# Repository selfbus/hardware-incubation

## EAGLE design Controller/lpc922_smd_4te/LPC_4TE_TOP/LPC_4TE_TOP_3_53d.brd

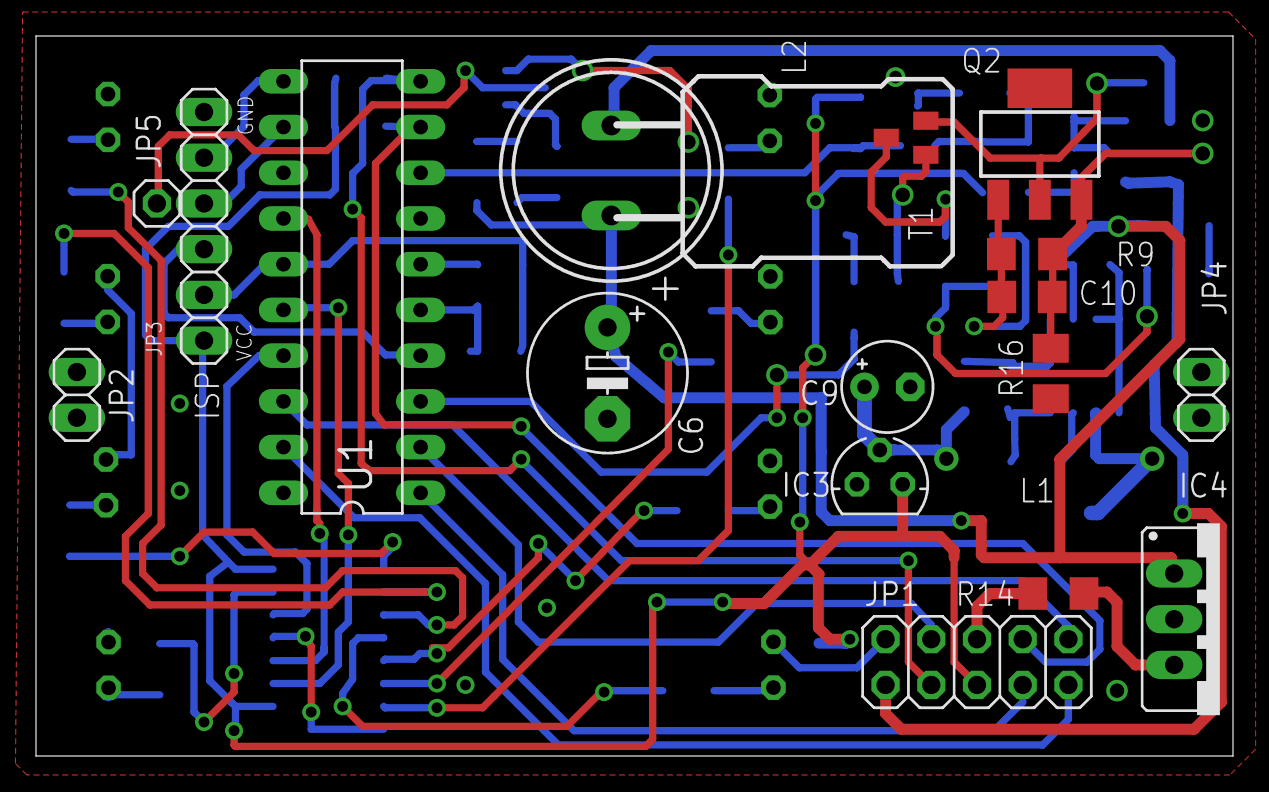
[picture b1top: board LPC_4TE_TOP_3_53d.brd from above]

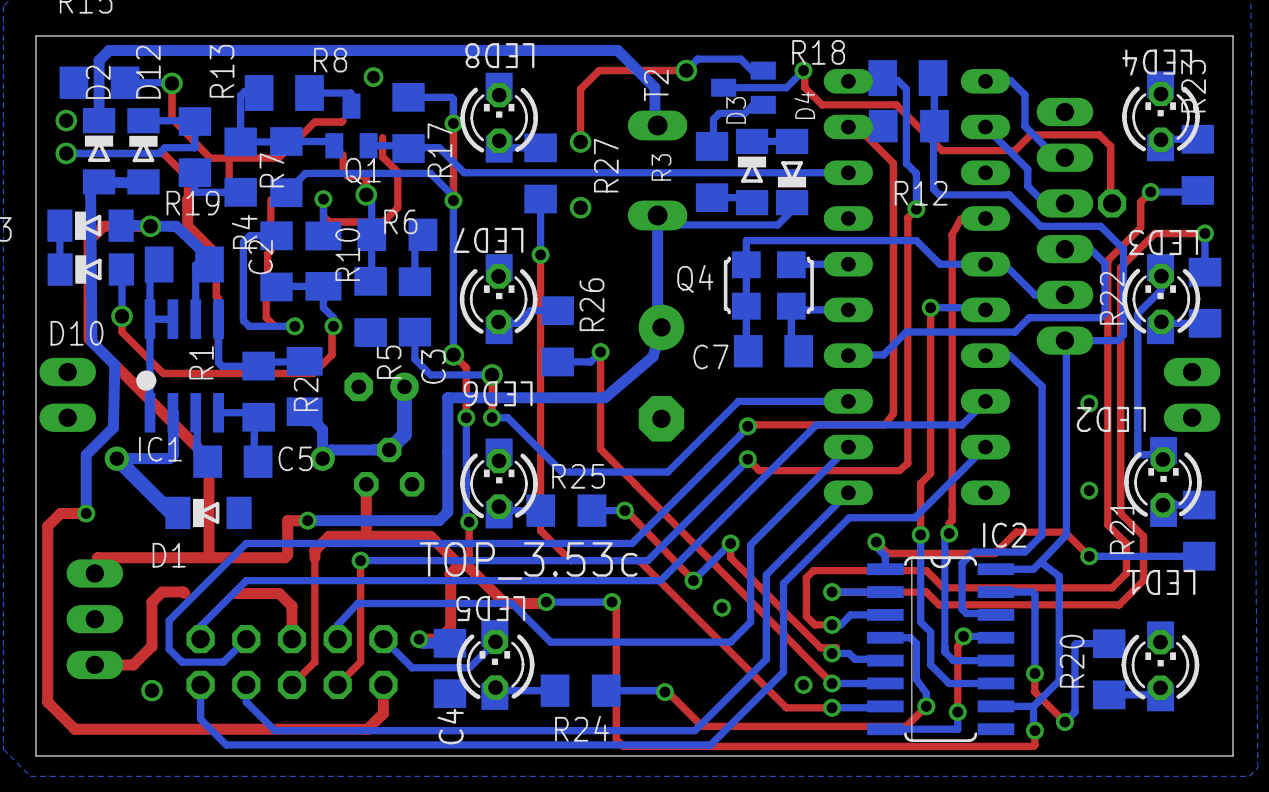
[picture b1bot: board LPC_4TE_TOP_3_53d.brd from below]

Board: 2 copper layers, 66.5 x 40.0 mm, 74 parts (56 on the bottom side), 58 nets.

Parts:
C2, C7: 100n; C1206
C3, C10: 10n; C1206
C4: 1µ16V; C1206
C5: 470p; C1206
C6: 100µ35V; E5-8,5
C9: 100µ16V; E2,5-5
D1: BAT46; MINIMELF
D2, D12: 1N4148; MINIMELF
D3: 12V; MINIMELF
D4, D10: 7,5V; MINIMELF
D13: 4148; MINIMELF
IC1: MC34063AD; SOIC8
IC2: 74HC595D; SO16
IC3: MCP1702-33; 79LXX
IC4: 7812; 78XXS
JP1: 2X05
JP2, JP4: 1X02
JP3: 1X06
JP5: 1X01
L1: 220µH; 2200-11.43
L2: 150mH; SD12_1000
LED1, LED2, LED3, LED4, LED5, LED6, LED7, LED8: LED3MM
LED9, LED10, LED11, LED12, LED13, LED14, LED15, LED16: CHIPLED_1206
Q1: BC856; SOT23-BEC
Q2: BCP52; SOT223
Q4: ASF
R1: 1k2; R1206
R2: 3k6; M1206
R3: 470k; R1206
R4, R9: 1k; R1206
R5: 100k; R1206
R6: 5k6; R1206
R7: 82k; R1206
R8: 47k; M1206
R10: 2k2; M1206
R12: 3k3; R1206
R13, R17: 10k; R1206
R14: ?; R1206
R15: 5R6; R1206
R16: 100k; M1206
R18: 3k3; M1206
R19: 3R3; M1206
R20, R21, R22, R23, R24, R25, R26, R27: R1206
T1, T2: BC848; SOT23
U1: 89LPC922; DIL20

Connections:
DRAIN: R10.1, T1.3
EIB+: D2.A, D12.A, JP1.1
EIBIN: Q1.E, R17.2, U1.8
EIB_DC: C6.+, D4.C, D13.A, IC1.6, IC4.IN, L2.2, R19.2
EIB_SEND: C3.2, U1.3
GATE: R5.2, R6.2, T1.1
GND: C4.1, C5.2, C6.-, C7.2, C9.-, D1.A, IC1.4, IC2.8, IC2.13, IC3.GND, IC4.GND, JP1.2, JP3.6, JP4.1, JP4.2, LED1.K, LED2.K, LED3.K, LED4.K, LED5.K, LED6.K, LED7.K, LED8.K, LED9.C, LED10.C, LED11.C, LED12.C, LED13.C, LED14.C, LED15.C, LED16.C, Q1.C, Q4.2, R1.1, R5.1, R8.1, R15.2, R16.1, T2.2, U1.5
INT0: JP1.8, R12.2, U1.9
unnamed: LED1.A, LED9.A, R20.2
unnamed: LED2.A, LED10.A, R21.2
unnamed: LED3.A, LED11.A, R22.2
unnamed: C10.1, Q2.1, R4.2, R9.1
unnamed: C3.1, R6.1
unnamed: C10.2, D12.C, Q2.3, R9.2, R13.2, R16.2
unnamed: Q2.2, R15.1, T1.2
unnamed: D2.C, L2.1
unnamed: JP3.5, U1.11
unnamed: LED4.A, LED12.A, R23.2
unnamed: LED5.A, LED13.A, R24.2
unnamed: IC4.OUT, R14.2
unnamed: LED6.A, LED14.A, R25.2
unnamed: LED7.A, LED15.A, R26.2
unnamed: JP3.3, U1.4
unnamed: D3.C, D4.A
unnamed: LED8.A, LED16.A, R27.2
unnamed: D3.A, R3.1
unnamed: R3.2, T2.1
unnamed: JP5.1, T2.3
unnamed: IC2.15, R20.1
unnamed: IC2.1, R21.1
unnamed: JP3.4, U1.12
unnamed: Q4.3, U1.6
unnamed: C9.+, IC3.IN, L1.1, R2.2
unnamed: IC2.2, R22.1
unnamed: IC2.3, R23.1
unnamed: IC2.7, R27.1
unnamed: C2.2, Q1.B, R7.1, R8.2
unnamed: IC2.6, R26.1
unnamed: IC2.5, R25.1
unnamed: IC2.4, R24.1
unnamed: IC1.5, R1.2, R2.1
unnamed: D1.C, IC1.2, L1.2
unnamed: C5.1, IC1.3
unnamed: D10.A, R4.1, R10.2
unnamed: D10.C, D13.C
unnamed: IC1.1, IC1.7, IC1.8, R19.1
unnamed: C2.1, R13.1
P0.0: JP1.7, U1.1
P0.2: JP1.9, U1.19
P0.3: JP1.10, U1.18
P04: IC2.14, U1.17
P05: IC2.11, U1.16
P06: IC2.12, U1.14
PROG: JP1.4, U1.2
PWM: JP1.3, R18.2, U1.10
VCC: C4.2, IC2.10, IC2.16, IC3.OUT, JP1.5, JP3.1, R7.2, R12.1, R17.1, R18.1
VCC_LPC: C7.1, JP3.2, Q4.1, Q4.4, U1.15
VDD: JP1.6, R14.1

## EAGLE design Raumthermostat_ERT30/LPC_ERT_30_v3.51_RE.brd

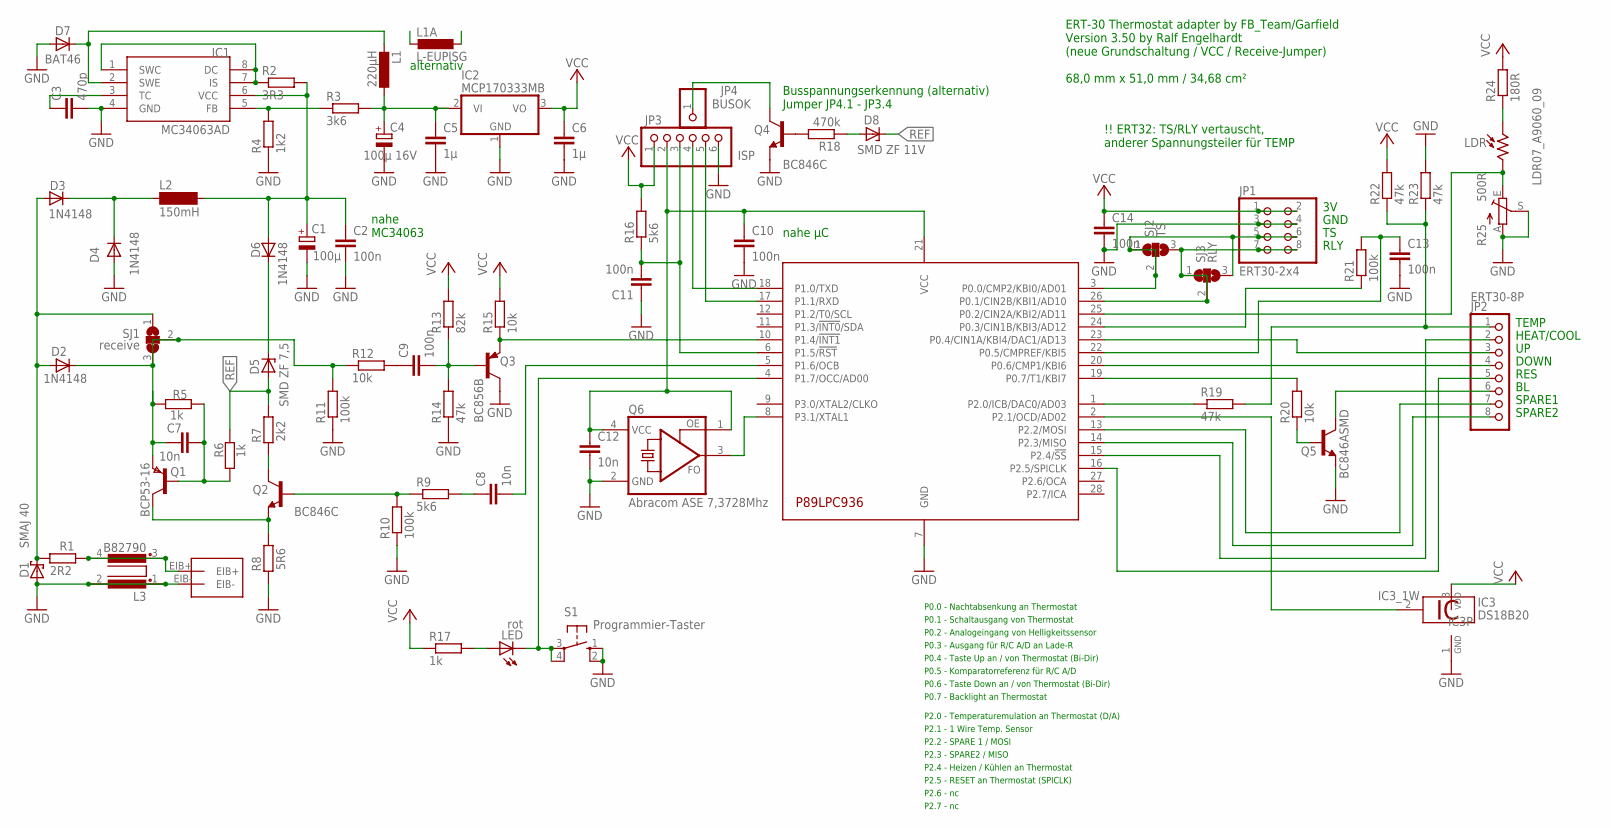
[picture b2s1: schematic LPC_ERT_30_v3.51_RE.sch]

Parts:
C1: 100µ; 153CLV-0605
C2, C9, C10, C11, C13, C14: 100n; C1206
C3: 470p; C1206
C4: 100µ 16V; 153CLV-0605
C5, C6: 1µ; C1206
C7, C8, C12: 10n; C1206
D1: SMAJ 40; SMB
D2, D3, D4, D6: 1N4148; MINIMELF
D5: SMD ZF 7,5; MINIMELF
D7: BAT46; MINIMELF
D8: SMD ZF 11V; MINIMELF
IC1: MC34063AD; SOIC8
IC2: MCP170333MB; SOT89
IC3: DS18B20; TO92-
JP1: ERT30-2x4; 2X04
JP2: ERT30-8P; PS-G-8
JP3: ISP; 1X06_SELFBUS
JP4: BUSOK; 1X01_SELFBUS
L1: 220µH; PIS24XX
L1A: L-EUPISG; PISG
L2: 150mH; SD12_1000
L3: B82790
LDR: LDR07_A9060_09; A90XX
LED: rot; CHIPLED_1206
LPC: P98LPC936 TSOP28; TSSOP28
Q1: BCP53-16; SOT223
Q2, Q4: BC846C; SOT23
Q3: BC856B; SOT23-BEC
Q5: BC846ASMD; SOT23
Q6: Abracom ASE 7,3728Mhz; ASFL3
R1: 2R2; R1206
R2: 3R3; R1206
R3: 3k6; R1206
R4: 1k2; R1206
R5, R6, R17: 1k; R1206
R7: 2k2; R1206
R8: 5R6; R1206
R9, R16: 5k6; R1206
R10, R11, R21: 100k; R1206
R12, R15, R20: 10k; R1206
R13: 82k; R1206
R14, R19, R22, R23: 47k; R1206
R18: 470k; R1206
R24: 180R; R1206
R25: 500R; CA6H
S1: Programmier-Taster; B3F-10XX
SJ1: receive; SJ_2
SJ2: TS; SJ_2
SJ3: RLY; SJ_2
U$5: EIB-CON

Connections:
+5V: C4.+, C5.1, IC2.2 (VI), IC2.2@1 (VI1), L1.2 (1), L1A.2, R3.2
/RST: C11.2, JP3.3, LPC.6 (P1.5/!RST), R16.1
AD0.3_TEMP: LPC.1 (P2.0/ICB/DAC0/AD03), R19.1
AD11_LDR: LDR.P$2 (2), LPC.25 (P0.2/CIN2A/KBI2/AD11), R25.E
AD12: LPC.24 (P0.3/CIN1B/KBI3/AD12), R21.1
BUS_OK: JP4.1, Q4.3 (C)
CLK: LPC.8 (P3.1/XTAL1), Q6.3 (FO)
CMP_REF: C13.1, LPC.22 (P0.5/CMPREF/KBI5), R21.2
EIB+: D1.C, D2.A, D3.A, R1.2, SJ1.1
GND: C1.-, C2.2, C3.2, C4.-, C5.2, C6.2, C10.2, C11.1, C12.2, C13.2, C14.2, D1.A, D4.A, D7.A, IC1.4 (GND), IC2.1 (GND), IC3.1 (GND), JP1.3, JP1.4, JP3.6, L3.1, L3.2, LPC.7 (GND), Q3.C, Q4.2 (E), Q5.2 (E), Q6.2 (GND), R4.1, R8.1, R10.1, R11.1, R14.1, R23.2, R25.A, R25.S, S1.1 (S), S1.2 (S1), U$5.EIB-
unnamed: C7.2, D2.C, Q1.3 (E), R5.2, R11.2, R12.1, SJ1.2, SJ1.3
unnamed: C9.2, Q3.B, R13.1, R14.2
unnamed: Q4.1 (B), R18.2
unnamed: Q2.3 (C), R7.1
unnamed: D3.C, D4.C, L2.1
unnamed: D8.A, R18.1
unnamed: C7.1, Q1.1 (B), R5.1, R6.2
unnamed: Q1.2 (C), Q1.4 (C), Q2.2 (E), R8.2
unnamed: C9.1, R12.2
unnamed: Q5.1 (B), R20.1
unnamed: JP2.6, Q5.3 (C)
unnamed: Q2.1 (B), R9.1, R10.2
unnamed: LDR.P$1 (1), R24.1
unnamed: C8.1, R9.2
unnamed: L3.3, L3.4, R1.1, U$5.EIB+
unnamed: D5.C, D6.C
unnamed: LED.A, R17.2
unnamed: JP2.1, R19.2, R22.1, R23.1
P0.0_TS: JP1.5, JP1.6, LPC.3 (P0.0/CMP2/KBI0/AD01), SJ2.1, SJ2.2, SJ3.3
P0.1_RLY: JP1.7, JP1.8, LPC.26 (P0.1/CIN2B/KBI1/AD10), SJ2.3, SJ3.1, SJ3.2
P0.4_UP: JP2.3, LPC.23 (P0.4/CIN1A/KBI4/DAC1/AD13)
P0.6_DOWN: JP2.4, LPC.20 (P0.6/CMP1/KBI6)
P0.7_BL: LPC.19 (P0.7/T1/KBI7), R20.2
P1.4_REC: LPC.10 (P1.4/!INT1), Q3.E, R15.1
P1.6_SENT: C8.2, LPC.5 (P1.6/OCB)
P1.7_PROG: LED.C, LPC.4 (P1.7/OCC/AD00), S1.3, S1.4 (P1)
P2.1_DS1820_1W1W: IC3.2 (1W), LPC.2 (P2.1/OCD/AD02)
P2.2_SPARE1: JP2.7, LPC.13 (P2.2/MOSI)
P2.3_SPARE2: JP2.8, LPC.14 (P2.3/MISO)
P2.4_HEAT_COOL: JP2.2, LPC.15 (P2.4/!SS)
P2.5_RST_ERT: JP2.5, LPC.16 (P2.5/SPICLK)
Q6: C10.1, C12.1, JP3.2, LPC.21 (VCC), Q6.1 (OE), Q6.4 (VCC)
REF: D5.A, D8.C, R6.1, R7.2
REF1.25V: IC1.5 (FB), R3.1, R4.2
RXD: JP3.5, LPC.17 (P1.1/RXD)
SWC_DC_IS: IC1.1 (SWC), IC1.7 (IS), IC1.8 (DC), R2.1
SWE: D7.C, IC1.2 (SWE), L1.1 (2), L1A.1
TC: C3.1, IC1.3 (TC)
TXD: JP3.4, LPC.18 (P1.0/TXD)
U_BUS: C1.+, C2.1, D6.A, IC1.6 (VCC), L2.2, R2.2
VCC: C6.1, C14.1, IC2.3 (VO), IC3.3 (VDD), JP1.1, JP1.2, JP3.1, R13.2, R15.2, R16.2, R17.1, R22.2, R24.2

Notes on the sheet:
ERT-30 Thermostat adapter by FB_Team/Garfield Version 3.50 by Ralf Engelhardt (neue Grundschaltung / VCC / Receive-Jumper) 68,0 mm x 51,0 mm / 34,68 cm²
nahe MC34063
RLY
GND
RES
DOWN
HEAT/COOL
TEMP
SPARE1
SPARE2
P0.0 - Nachtabsenkung an Thermostat
P0.1 - Schaltausgang von Thermostat
P0.2 - Analogeingang von Helligkeitssensor
P0.3 - Ausgang für R/C A/D an Lade-R
P0.4 - Taste Up an / von Thermostat (Bi-Dir)
P0.5 - Komparatorreferenz für R/C A/D
P0.6 - Taste Down an / von Thermostat (Bi-Dir)
P0.7 - Backlight an Thermostat
P2.0 - Temperaturemulation an Thermostat (D/A)
P2.1 - 1 Wire Temp. Sensor
P2.2 - SPARE 1 / MOSI
P2.3 - SPARE2 / MISO
P2.4 - Heizen / Kühlen an Thermostat
P2.5 - RESET an Thermostat (SPICLK)
P2.6 - nc
P2.7 - nc
nahe µC
!! ERT32: TS/RLY vertauscht, anderer Spannungsteiler für TEMP
alternativ
Busspannungserkennung (alternativ) Jumper JP4.1 - JP3.4

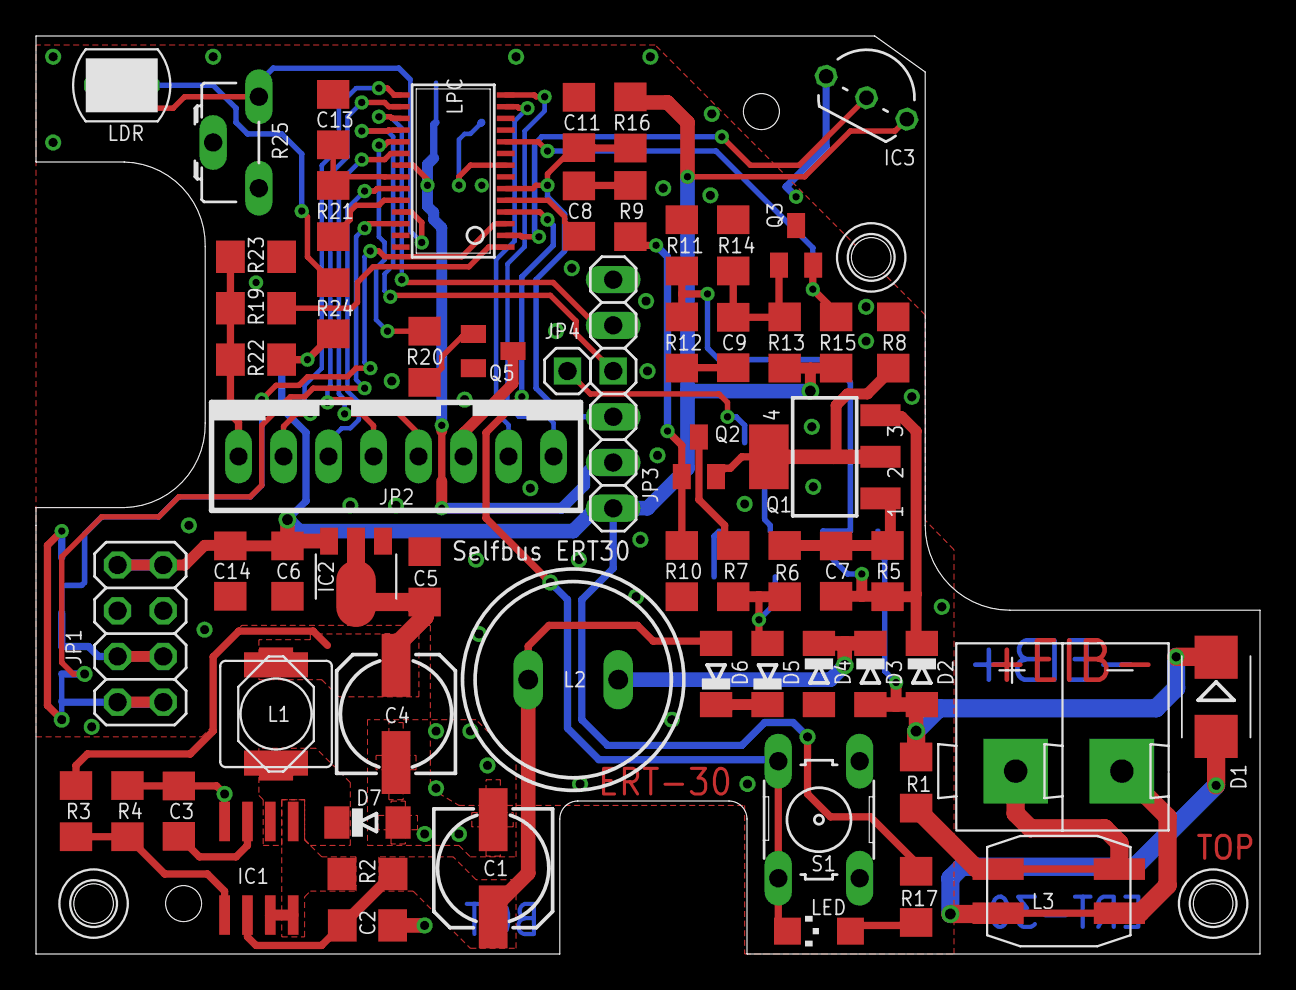
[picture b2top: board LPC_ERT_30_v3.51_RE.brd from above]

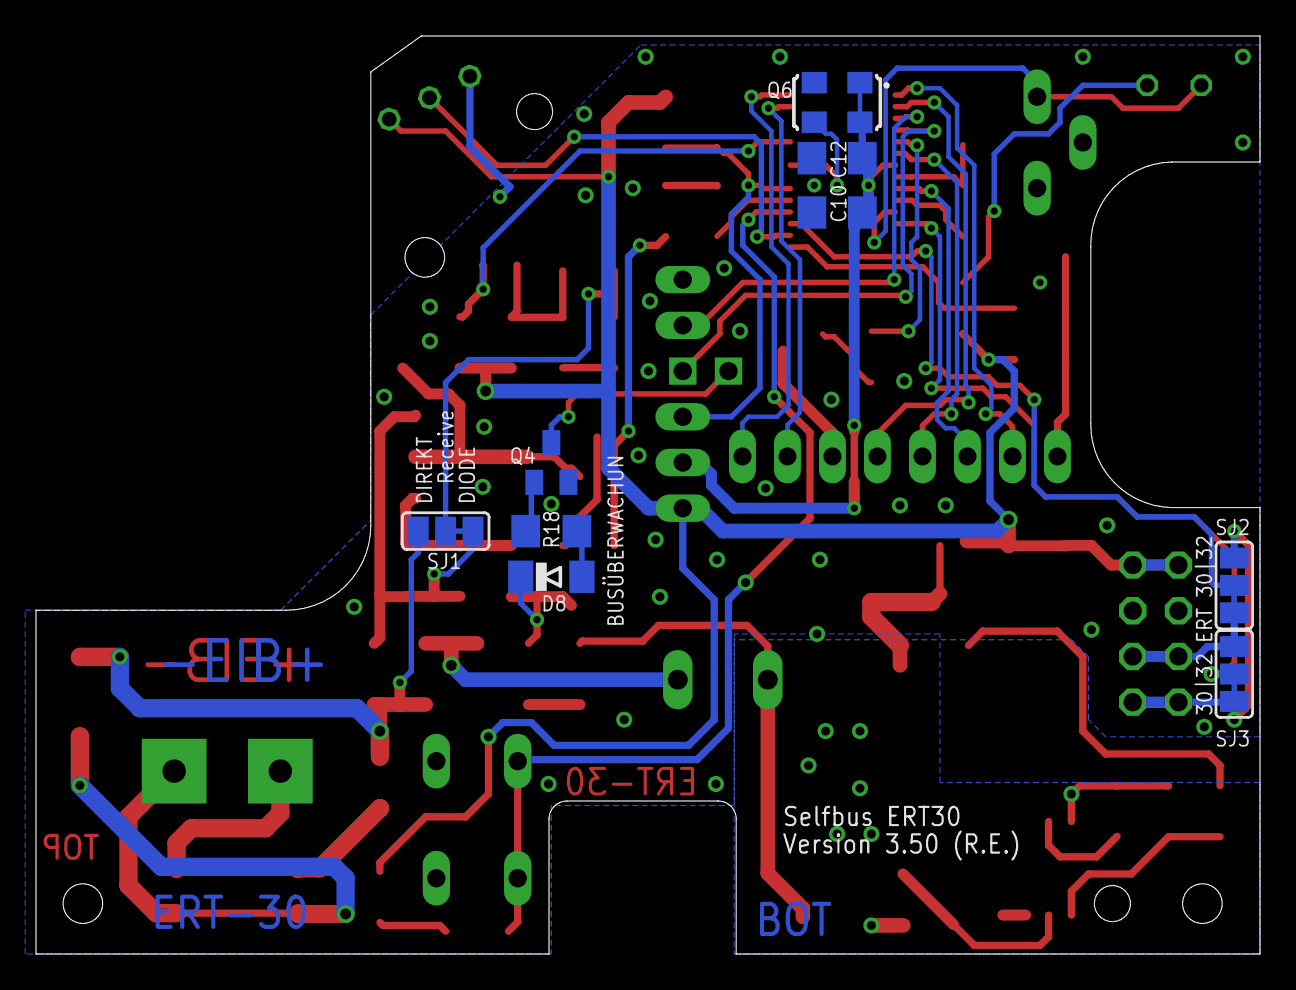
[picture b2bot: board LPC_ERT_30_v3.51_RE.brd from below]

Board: 2 copper layers, 68.0 x 51.0 mm, 75 parts (9 on the bottom side), 51 nets.

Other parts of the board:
U$2, U$9, U$10: 2,2

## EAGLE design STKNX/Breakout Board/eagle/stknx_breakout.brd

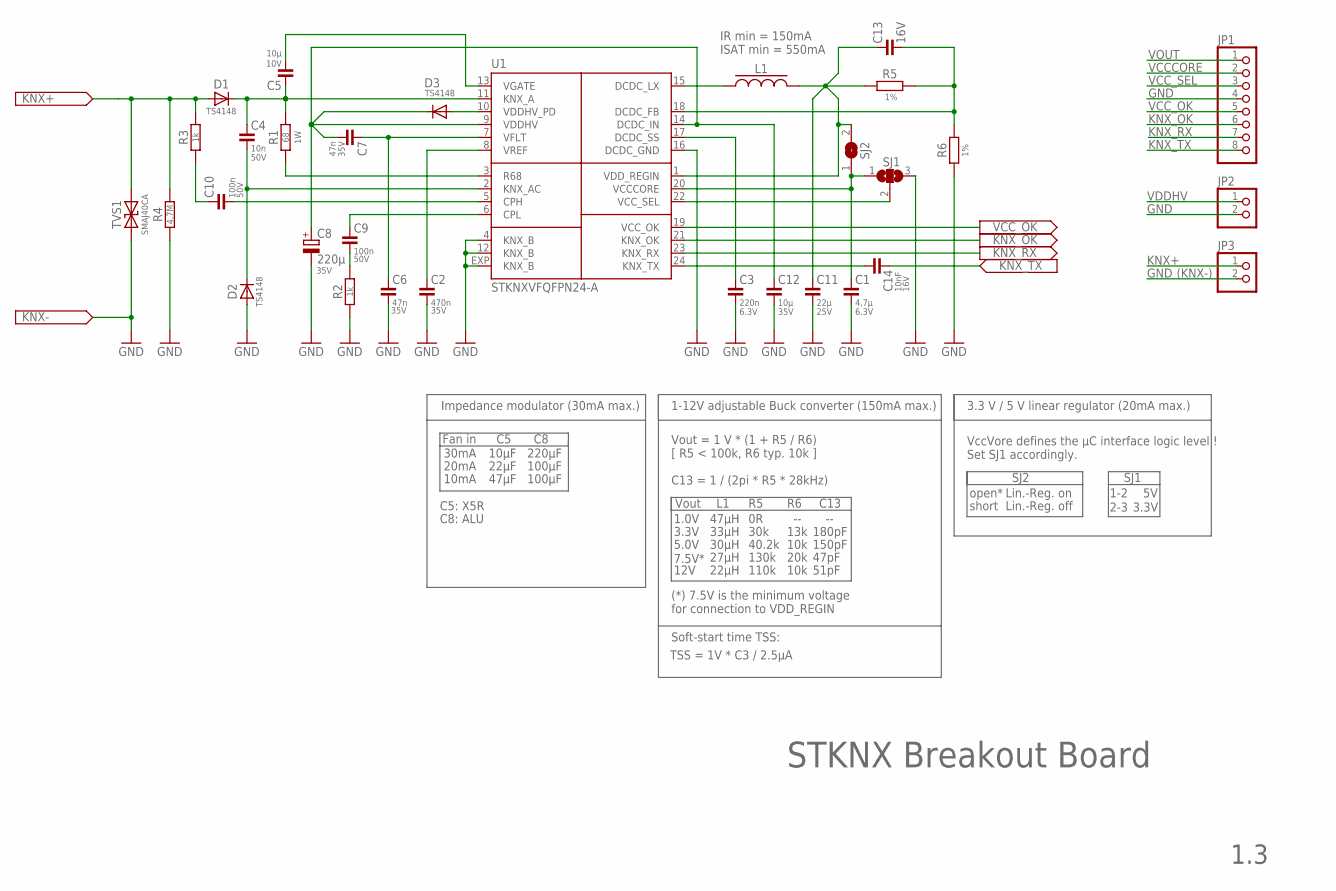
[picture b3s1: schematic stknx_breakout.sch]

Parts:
C1: 4,7µ; C0805; VOLTAGE 6.3V
C2: 470n; C0805; VOLTAGE 35V
C3: 220n; C0805; VOLTAGE 6.3V
C4: 10n; C0805; VOLTAGE 50V
C5: 10µ; C0805; VOLTAGE 10V
C6, C7: 47n; C0805; VOLTAGE 35V
C8: 220µ; PANASONIC_F; VOLTAGE 35V
C9, C10: 100n; C0805; VOLTAGE 50V
C11: 22µ; C0805; VOLTAGE 25V
C12: 10µ; C0805; VOLTAGE 35V
C13: C13; C0805; VOLTAGE 16V
C14: 10nF; C0805; VOLTAGE 16V
D1, D2, D3: TS4148; 0805
JP1: PINHD-1X8; 1X08
JP2, JP3: PINHD-1X2; 1X02
L1: L1; WE-LQS_4025
R1: 68; R1218
R2, R3: 1k; R0805
R4: 4.7M; R0805
R5: R5; R0805; TOLERANCE 1%
R6: R6; R0805; TOLERANCE 1%
SJ1: SJ2WW; SJ_2W
SJ2: SJW
TVS1: SMAJ40CA; DO-214AC(SMA)
U1: STKNXVFQFPN24-A; VFQFPN24-A

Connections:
DCDC_FB: C13.2, R5.2, R6.2, U1.18 (DCDC_FB)
DCDC_SS: C3.1, U1.17 (DCDC_SS)
GND: C1.2, C2.2, C3.2, C6.2, C8.-, C11.2, C12.2, D2.A, JP1.4, JP2.2, JP3.2, R2.1, R4.1, R6.1, SJ1.3, TVS1.2 (A2), U1.4 (KNX_B), U1.12 (KNX_B), U1.16 (DCDC_GND), U1.EXP (KNX_B)
KNX+: D1.A, JP3.1, R3.2, R4.2, TVS1.1 (A1)
KNX_OK: JP1.6, U1.21 (KNX_OK)
KNX_RX: JP1.7, U1.23 (KNX_RX)
KNX_TX: C14.2, JP1.8
KNX_TX_1: C14.1, U1.24 (KNX_TX)
unnamed: C2.1, U1.8 (VREF)
unnamed: C6.1, C7.1, U1.7 (VFLT)
unnamed: R1.1, U1.3 (R68)
unnamed: C4.2, D2.C, U1.2 (KNX_AC)
unnamed: C4.1, C5.1, D1.C, R1.2, U1.11 (KNX_A)
unnamed: D3.A, U1.10 (VDDHV_PD)
unnamed: C9.2, R2.2
unnamed: C9.1, U1.6 (CPL)
unnamed: C10.1, R3.1
unnamed: C10.2, U1.5 (CPH)
unnamed: L1.1, U1.15 (DCDC_LX)
VCCCORE: C1.1, JP1.2, SJ1.1, SJ2.1, U1.20 (VCCCORE)
VCC_OK: JP1.5, U1.19 (VCC_OK)
VCC_SEL: JP1.3, SJ1.2, U1.22 (VCC_SEL)
VDDHV: C7.2, C8.+, C12.1, D3.C, JP2.1, U1.9 (VDDHV), U1.14 (DCDC_IN)
VGATE: C5.2, U1.13 (VGATE)
VOUT: C11.1, C13.1, JP1.1, L1.2, R5.1, SJ2.2, U1.1 (VDD_REGIN)

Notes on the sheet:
SJ1
1-2
2-3
3.3V
5.0V
7.5V*
12V
33µH
27µH
22µH
30µH
SJ2
open*
short
Lin.-Reg. on
Lin.-Reg. off
Vout
C13
30k
13k
180pF
1.3
STKNX Breakout Board
Vout = 1 V * (1 + R5 / R6) [ R5 < 100k, R6 typ. 10k ] C13 = 1 / (2pi * R5 * 28kHz)
VccVore defines the µC interface logic level ! Set SJ1 accordingly.
1.0V
47µH
(*) 7.5V is the minimum voltage for connection to VDD_REGIN
40.2k
10k
150pF
130k
20k
47pF
110k
51pF
Soft-start time TSS:
3.3 V / 5 V linear regulator (20mA max.)
1-12V adjustable Buck converter (150mA max.)
TSS = 1V * C3 / 2.5µA

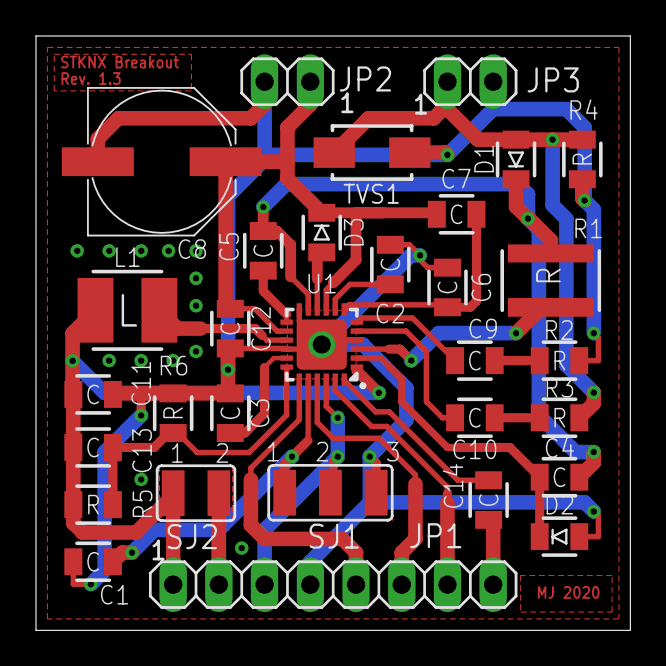
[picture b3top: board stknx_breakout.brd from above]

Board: 2 copper layers, 33.0 x 33.0 mm, 31 parts (0 on the bottom side), 25 nets.
